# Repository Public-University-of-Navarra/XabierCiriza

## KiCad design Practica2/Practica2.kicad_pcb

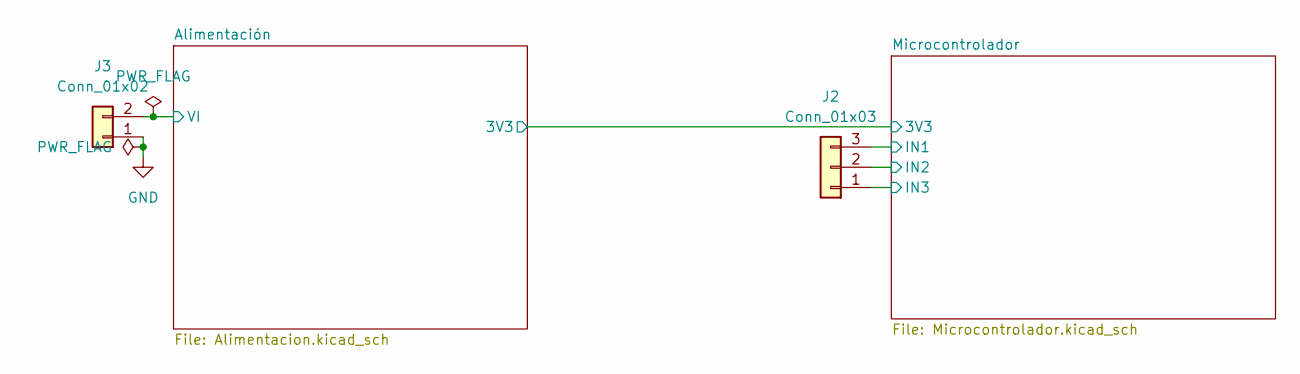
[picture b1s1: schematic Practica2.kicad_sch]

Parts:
J2: Conn_01x03; PinHeader_1x03_P2.54mm_Vertical
J3: Conn_01x02; PinHeader_1x02_P2.54mm_Vertical

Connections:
/Alimentación/VI: J3.2; also elsewhere on the board
/Microcontrolador/IN1: J2.3; also elsewhere on the board
/Microcontrolador/IN2: J2.2; also elsewhere on the board
/Microcontrolador/IN3: J2.1; also elsewhere on the board
GND: J3.1; also elsewhere on the board

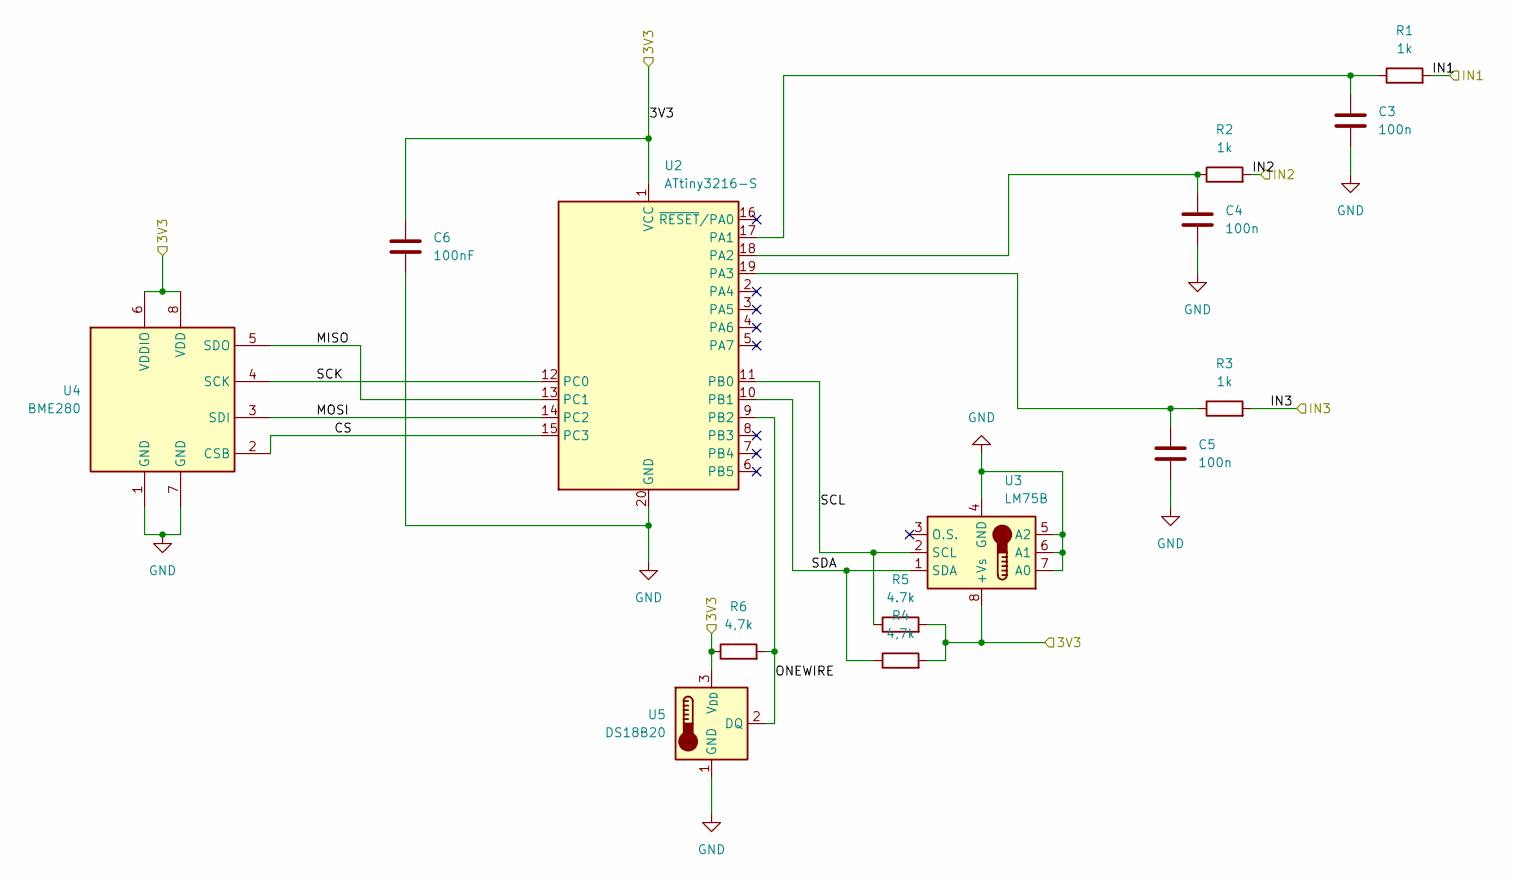
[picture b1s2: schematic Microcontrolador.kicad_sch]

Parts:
C3, C4, C5: 100n; C_0603_1608Metric
C6: 100nF; C_0603_1608Metric
R1, R2, R3: 1k; R_0603_1608Metric
R4, R6: 4,7k; R_0603_1608Metric
R5: 4.7k; R_0603_1608Metric
U2: ATtiny3216-S; SOIC-20W_7.5x12.8mm_P1.27mm; MPN ATTINY3216-SN
U3: LM75B; VSSOP-8_2.3x2mm_P0.5mm
U4: BME280; Bosch_LGA-8_2.5x2.5mm_P0.65mm_ClockwisePinNumbering
U5: DS18B20; TO-92_Inline

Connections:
/Microcontrolador/3V3: C6.1, R4.2, R5.2, R6.1, U2.1 (VCC), U3.8 (+Vs), U4.6 (VDDIO), U4.8 (VDD), U5.3 (V_{DD}); also elsewhere on the board
/Microcontrolador/CS: U2.15 (PC3), U4.2 (CSB)
/Microcontrolador/IN1: R1.2; also elsewhere on the board
/Microcontrolador/IN2: R2.2; also elsewhere on the board
/Microcontrolador/IN3: R3.2; also elsewhere on the board
/Microcontrolador/MISO: U2.13 (PC1), U4.5 (SDO)
/Microcontrolador/MOSI: U2.14 (PC2), U4.3 (SDI)
/Microcontrolador/ONEWIRE: R6.2, U2.9 (PB2), U5.2 (DQ)
/Microcontrolador/SCK: U2.12 (PC0), U4.4 (SCK)
/Microcontrolador/SCL: R5.1, U2.11 (PB0), U3.2 (SCL)
/Microcontrolador/SDA: R4.1, U2.10 (PB1), U3.1 (SDA)
GND: C3.2, C4.2, C5.2, C6.2, U2.20 (GND), U3.4 (GND), U3.5 (A2), U3.6 (A1), U3.7 (A0), U4.1 (GND), U4.7 (GND), U5.1 (GND); also elsewhere on the board
unnamed: C3.1, R1.1, U2.17 (PA1)
unnamed: C4.1, R2.1, U2.18 (PA2)
unnamed: C5.1, R3.1, U2.19 (PA3)

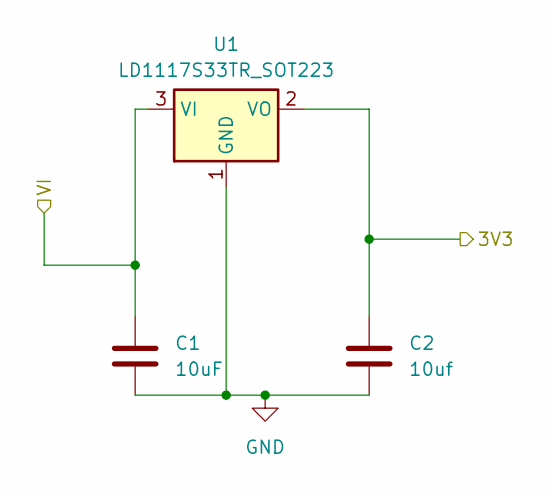
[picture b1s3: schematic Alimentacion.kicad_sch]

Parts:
C1: 10uF; C_0805_2012Metric
C2: 10uf; C_0805_2012Metric
U1: LD1117S33TR_SOT223; SOT-223-3_TabPin2; MPN LD1117S33TR

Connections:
/Alimentación/VI: C1.1, U1.3 (VI); also elsewhere on the board
/Microcontrolador/3V3: C2.1, U1.2 (VO); also elsewhere on the board
GND: C1.2, C2.2, U1.1 (GND); also elsewhere on the board

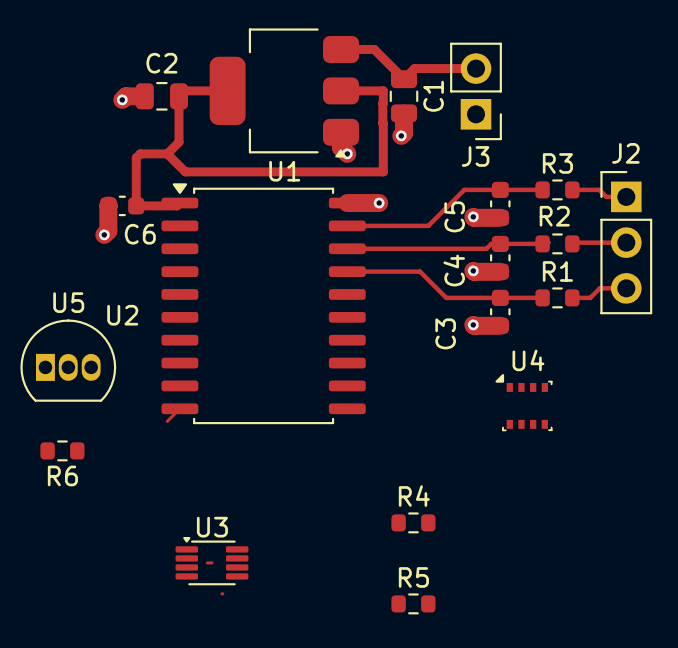
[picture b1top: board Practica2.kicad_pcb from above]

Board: 4 copper layers, 19 parts (0 on the bottom side), 16 nets.
